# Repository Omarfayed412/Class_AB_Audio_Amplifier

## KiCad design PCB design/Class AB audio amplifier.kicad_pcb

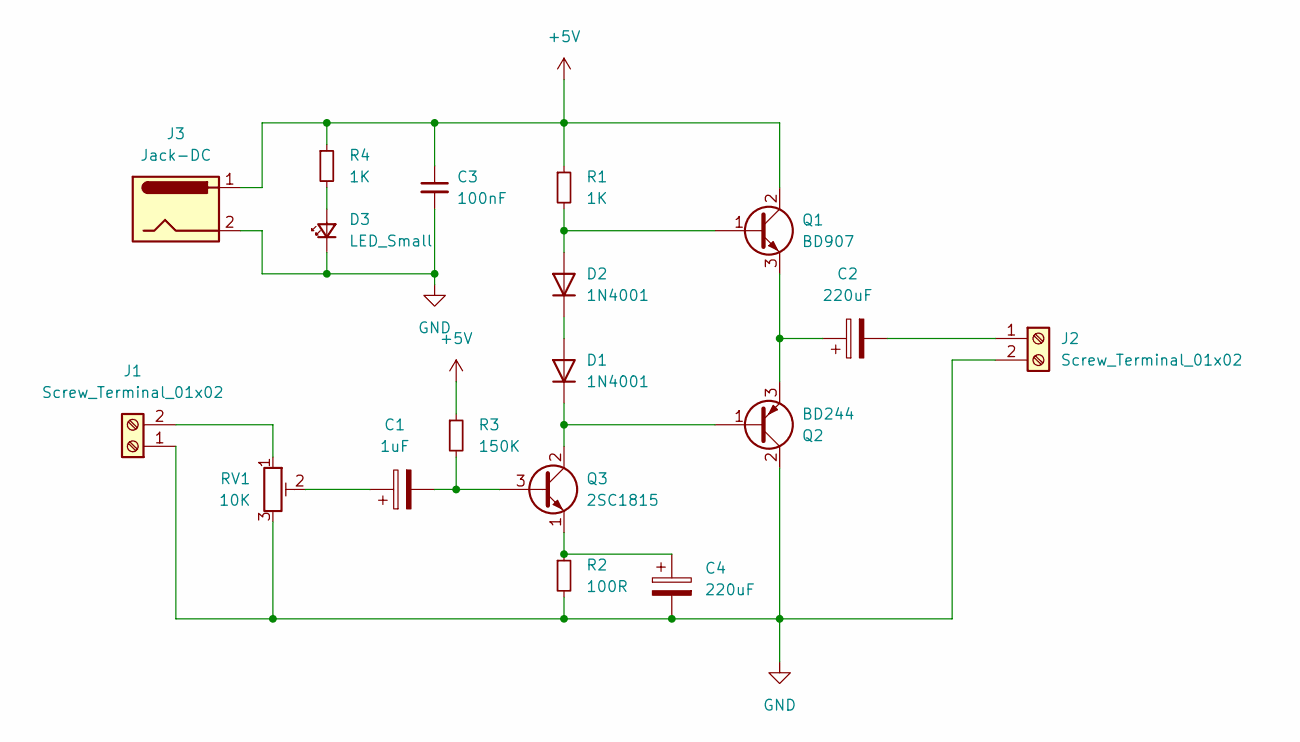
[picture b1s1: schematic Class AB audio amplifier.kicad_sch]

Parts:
C1: 1uF; CP_Radial_D8.0mm_P3.50mm
C2, C4: 220uF; CP_Radial_D14.0mm_P5.00mm
C3: 100nF; C_0603_1608Metric
D1, D2: 1N4001; D_DO-41_SOD81_P10.16mm_Horizontal
D3: LED_Small; LED_0805_2012Metric
J1, J2: Screw_Terminal_01x02; TerminalBlock_bornier-2_P5.08mm
J3: Jack-DC; BarrelJack_GCT_DCJ200-10-A_Horizontal
Q1: BD907; TO-220-3_Vertical
Q2: BD244; TO-220-3_Vertical
Q3: 2SC1815; TO-92_Inline
R1, R4: 1K; R_0603_1608Metric
R2: 100R; R_0603_1608Metric
R3: 150K; R_0603_1608Metric
RV1: 10K; Potentiometer_Alps_RK163_Single_Horizontal

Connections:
+5V: C3.1, J3.1, Q1.2 (C), R1.1, R3.1, R4.1
GND: C3.2, C4.2, D3.1 (K), J1.1, J2.2, J3.2, Q2.2 (C), R2.2, RV1.3
unnamed: C1.1, RV1.2
unnamed: D1.2 (A), D2.1 (K)
unnamed: D1.1 (K), Q2.1 (B), Q3.2 (C)
unnamed: D2.2 (A), Q1.1 (B), R1.2
unnamed: D3.2 (A), R4.2
unnamed: J1.2, RV1.1
unnamed: C2.2, J2.1
unnamed: C2.1, Q1.3 (E), Q2.3 (E)
unnamed: C1.2, Q3.3 (B), R3.2
unnamed: C4.1, Q3.1 (E), R2.1

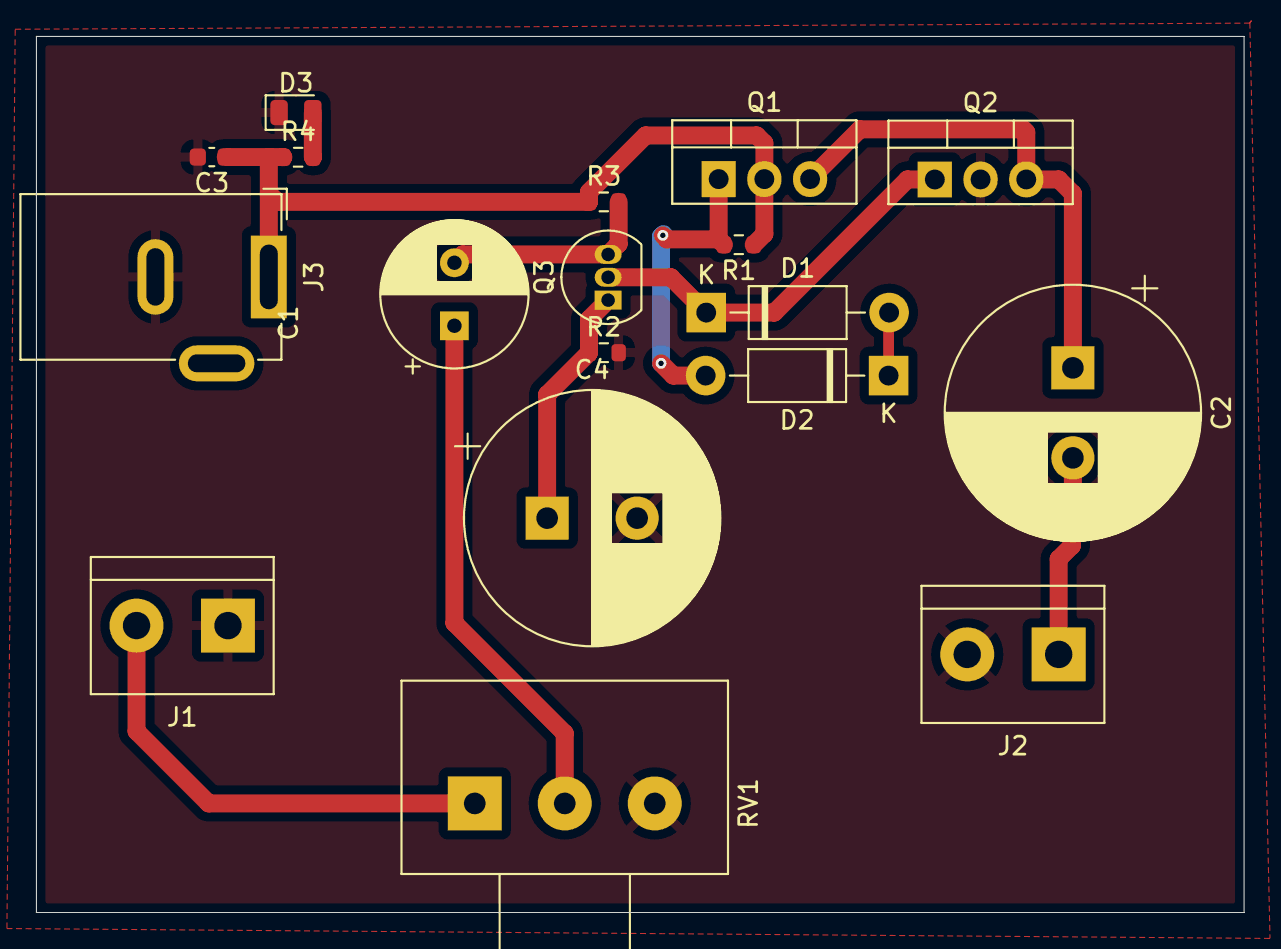
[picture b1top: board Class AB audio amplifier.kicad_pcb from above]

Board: 2 copper layers, 67.1 x 48.7 mm, 18 parts (0 on the bottom side), 12 nets.

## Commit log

2024-12-24 Simulation + Oscilloscope readings
2024-12-24 PCB design files in Kicad added
